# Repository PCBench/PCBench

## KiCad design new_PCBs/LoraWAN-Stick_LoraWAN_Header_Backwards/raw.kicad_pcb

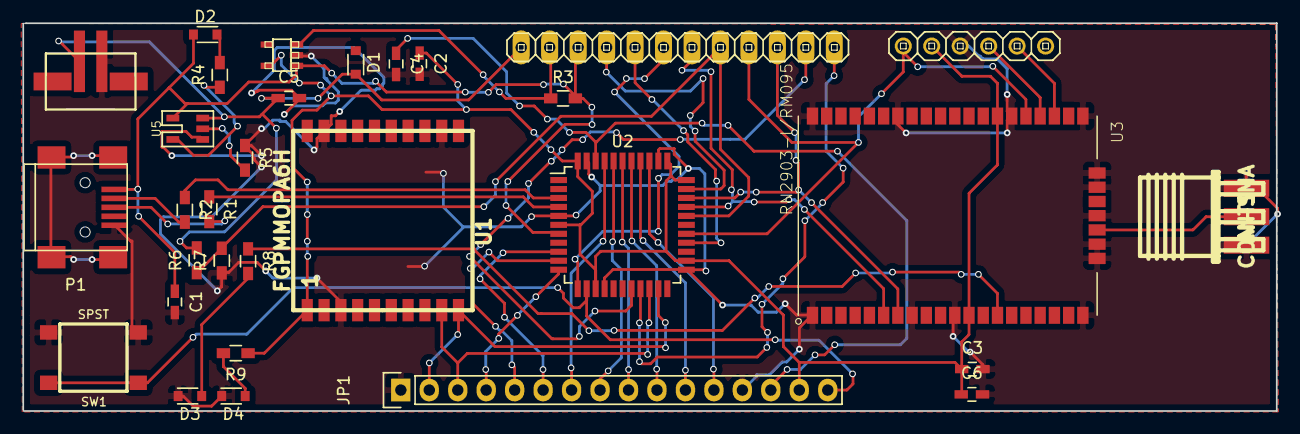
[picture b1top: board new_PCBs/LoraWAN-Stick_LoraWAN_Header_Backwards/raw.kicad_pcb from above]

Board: 2 copper layers, 111.9 x 34.6 mm, 31 parts (0 on the bottom side), 40 nets.

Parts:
ANT1: CON-SMA; CON-SMA-EDGE
C1, C2, C5, C6: 10uF; C_0603_HandSoldering
C3, C4: 1uF; C_0603_HandSoldering
CN1: JST_2PIN-SMT; adafruit-JST-PH-2-SMT
D1: DIODESCH; D_0805
D2: LED-BAT; D_0805
D3: LED-RED; D_0805
D4: LED-POW; D_0805
JP1: CONN_01X16; Pin_Header_Straight_1x16
JP2: PINHD-1X6; adafruit-1X06
JP3: PINHD-1X12; adafruit-1X12
P1: USB_OTG; USB_Mini-B
R1, R2: 22; R_0603_HandSoldering
R3, R6, R7: 100k; R_0603_HandSoldering
R4, R8, R9: 1k; R_0603_HandSoldering
R5: 10k; R_0603_HandSoldering
SW1: SPST; SW_PUSH_SMD
U1: FGPMMOPA6H
U2: ATmega32U4-AU; TQFP-44_10x10mm_Pitch0.8mm
U3: RN2903-I/RM095; XCVR_RN2903-I%2fRM095
U4: SPX3819
U5: MCP73831

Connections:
3v3: C2.1, C3.1, C6.1, JP1.15, JP2.2, R9.1, U1.1, U2.6, U2.14, U2.24, U2.33, U2.34, U2.44, U3.12, U3.34, U4.4
9: JP3.8, R6.1, R7.2, U2.29
/0: JP1.3, U1.9, U2.20
/1: JP1.2, U1.10, U2.21
/2: JP3.12, U2.19
/3: JP3.11, U2.18
/5: JP3.10, U2.31, U3.7
/6: JP2.1, JP3.9, U2.27, U3.32
/10: JP3.7, U2.30, U3.6
/11: JP3.6, U2.12
/12: JP3.5, U2.26
/13: JP3.4, U2.32
/A0: JP1.12, U2.36
/A1: JP1.11, U2.37
/A2: JP1.10, U2.38
/A3: JP1.9, U2.39
/A4: JP1.8, U2.40
/A5: JP1.7, U2.41
/EN: JP3.2, R3.1, U4.3
/MISO: JP1.4, U2.11
/MOSI: JP1.5, U2.10
/SCK: JP1.6, U2.9
/TEST0: JP2.5, U3.30
/TEST1: JP2.4, U3.31
ARFF: C4.1, JP1.14, U2.42
GND: ANT1.2, ANT1.3, ANT1.4, ANT1.5, C1.2, C2.2, C3.2, C4.2, C5.2, C6.2, CN1.1, D3.1, D4.1, JP1.1, JP1.13, JP2.3, P1.5, R5.1, R7.1, SW1.2, U1.3, U1.12, U1.19, U2.5, U2.15, U2.23, U2.35, U2.43, U3.1, U3.8, U3.11, U3.20, U3.21, U3.22, U3.24, U3.26, U3.27, U3.28, U3.33, U3.41, U3.47, U4.2, U5.2
unnamed: ANT1.1, U3.23
unnamed: D2.1, R4.2
unnamed: D3.2, R8.2
unnamed: D4.2, R9.2
unnamed: P1.2, R2.2
unnamed: P1.3, R1.2
unnamed: R1.1, U2.4
unnamed: R2.1, U2.3
unnamed: R4.1, U5.1
unnamed: R5.2, U5.5
unnamed: R8.1, U3.14
RST: JP1.16, SW1.1, U2.13
VBAT: C5.1, CN1.2, D1.1, JP3.1, R6.2, U5.3
VBUS: C1.1, D2.2, JP3.3, P1.1, R3.2, U2.7, U4.1, U5.4

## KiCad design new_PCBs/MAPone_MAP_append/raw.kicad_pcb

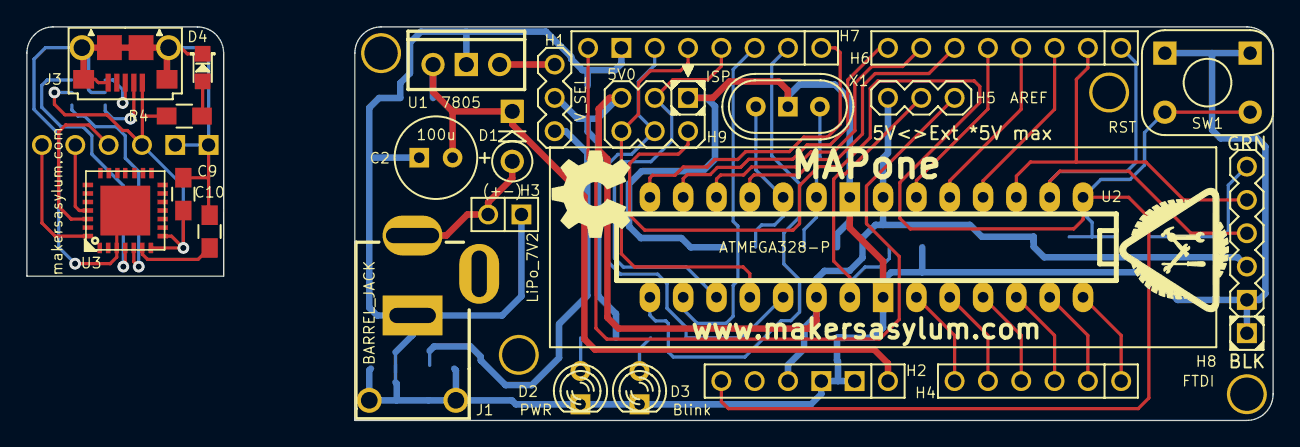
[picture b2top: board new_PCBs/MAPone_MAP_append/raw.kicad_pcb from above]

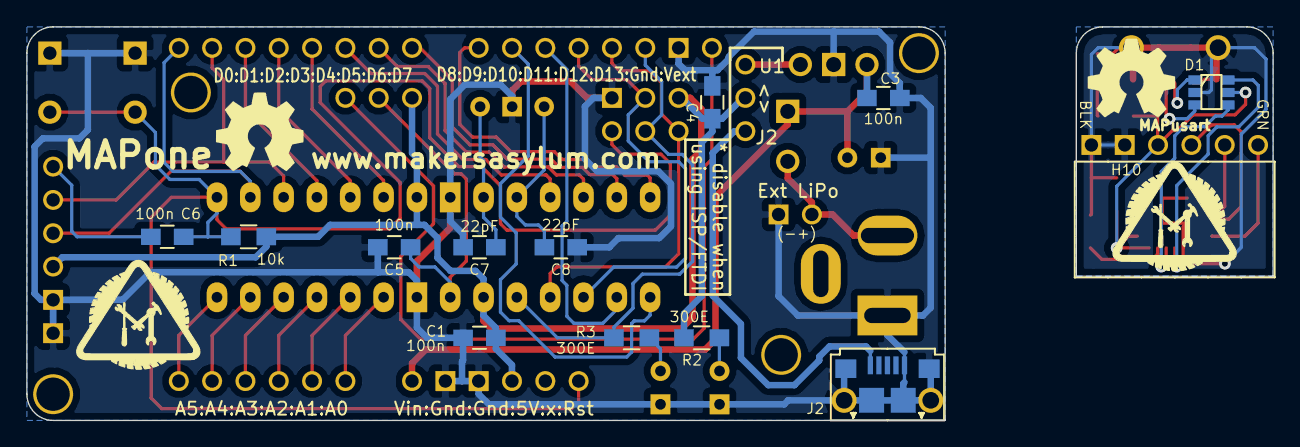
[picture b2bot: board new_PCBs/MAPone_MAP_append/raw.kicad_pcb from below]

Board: 2 copper layers, 70.0 x 30.0 mm, 47 parts (17 on the bottom side), 41 nets.

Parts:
C1, C3, C4, C5, C6, C9, C10: 100n; C_0805_HandSoldering
C2: 100u; Elko_vert_11.2x6.3mm_RM2.5
C7, C8: 22pF; C_0805_HandSoldering
D1: 1N4007; Diode_DO-41_SOD81_Vertical_KathodeUp
D1#2: USBLC6-2; SOT-23-6
D2: PWR; LED-3MM
D3: Blink; LED-3MM
D4: LED_USB; LED-0805
H1: V_SEL; Header_3
H2: Power; Socket_Strip_Straight_1x06
H3: LiPo_7V2; Pin_Header_Straight_1x02
H4: ANALOG; Socket_Strip_Straight_1x06
H5: AREF; Header_A_REF
H6: IO_L; Socket_Strip_Straight_1x08
H7: IO_H; Socket_Strip_Straight_1x08
H8: FTDI; Header_FTDI
H9: ISP; Header_ICSP
H10: FTDI; Socket_Strip_Angled_1x06
J1: BARREL_JACK; JACK_ALIM
J2, J3: USB-Micro; USB_B_Micro
P1, P2, P3, P4: CONN_1; vite_3mm
R1: 10k; R_0805_HandSoldering
R2, R3, R4: 300E; R_0805_HandSoldering
SW1: RST; SW-PB
U1: 7805; LM78XXV
U2: ATMEGA328-P; DIP-28__300_ELL_ZIF
U3: CP210X; qfn-28
X1: 16MHz; Crystal_HC49-U_Vertical_3Pin
Z1, Z2: CONN_1; MA_Logo2
Z3: SCREW; MA_Logo2
Z5: SCREW; OSHW_6mm
Z6, Z7: CONN_1; OSHW_6mm

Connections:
/3V3: C10.1, U3.6
/5V: C1.1, C4.1, C9.1, D1#2.5, H1.2, H2.4, H5.1, H8.3, H9.2, H10.3, J3.1, R1.1, R2.2, R4.1, U2.7, U2.20, U3.7, U3.8
/AD0: H4.6, U2.23
/AD1: H4.5, U2.24
/AD2: H4.4, U2.25
/AD3: H4.3, U2.26
/AD4_SDA: H4.2, U2.27
/AD5_SCL: H4.1, U2.28
/AREF: C5.1, H5.2, U2.21
/D+: D1#2.6, U3.4
/D+IN: D1#2.1, J3.3
/D-: D1#2.4, U3.5
/D-IN: D1#2.3, J3.2
/GND_U: C9.2, C10.2, D1#2.2, D4.2, H10.1, H10.2, J3.5, J3.T1, J3.T2, J3.T3, J3.T4, J3.T5, J3.T6, U3.3, U3.29
/MISO: H7.5, H9.1, U2.18
/MOSI_P: H7.4, H9.4, U2.17
/PB0: H7.1, U2.14
/PB1_P: H7.2, U2.15
/PD2: H6.3, U2.4
/PD3_P: H6.4, U2.5
/PD4: H6.5, U2.6
/PD5_P: H6.6, U2.11
/PD6_P: H6.7, U2.12
/PD7: H6.8, U2.13
/RST: C6.1, H2.6, H9.5, H10.6, R1.2, SW1.2, U2.1, U3.28
/RXD: H6.1, H8.4, H10.5, U2.2, U3.25
/SCK: H7.6, H9.3, R3.1, U2.19
/SS_P: H7.3, U2.16
/TXD: H6.2, H8.5, H10.4, U2.3, U3.26
/V_IN: C2.1, C3.2, D1.2, H2.1, U1.VI
/V_REG: H1.1, U1.VO
/V_USB: H1.3, J2.1
/Vext: H5.3, H7.8
GND: C1.2, C2.2, C3.1, C4.2, C5.2, C7.2, C8.2, D2.2, D3.2, H2.2, H2.3, H3.1, H7.7, H8.1, H8.2, H9.6, J1.2, J2.5, J2.T1, J2.T2, J2.T3, J2.T4, J2.T5, J2.T6, SW1.1, U1.GND, U2.8, U2.22, X1.3
unnamed: C6.2, H8.6
unnamed: C7.1, U2.9, X1.1
unnamed: C8.1, U2.10, X1.2
unnamed: D1.1, H3.2, J1.1
unnamed: D2.1, R2.1
unnamed: D3.1, R3.2
unnamed: D4.1, R4.2

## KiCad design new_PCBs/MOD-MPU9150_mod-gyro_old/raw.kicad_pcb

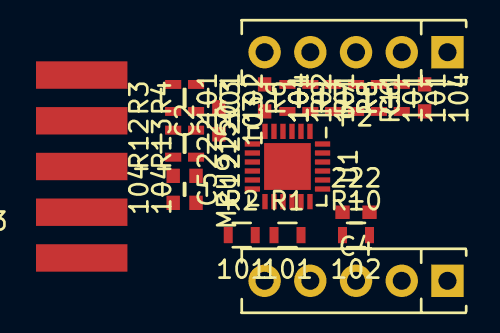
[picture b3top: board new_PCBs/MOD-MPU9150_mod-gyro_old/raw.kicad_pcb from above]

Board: 2 copper layers, 23 parts (0 on the bottom side), 20 nets, no tracks yet.

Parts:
C1, C3, C5, C6: 104; C_0603
C2: 103; C_0603
C4: 222; C_0603
P1, P2: CONN_01X05; SIP5_Housing
P3: HE10-10; UEXTF
R1, R2, R3, R4, R5, R6, R7, R8: 101; R_0603
R9, R10, R11: 102; R_0603
R12, R13: 222; R_0603
U1: MPU9150; QFN-24-1EP_4x4mm_Pitch0.5mm

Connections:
/SCL: P3.5, R4.1, R13.2
/SDA: P3.6, R3.1, R12.2
CLKIN: P2.4, R8.1, R11.1
GND: C1.2, C2.2, C3.2, C4.1, C5.2, C6.2, P1.1, P2.5, P3.2, R9.2, R10.2, R11.2, U1.15, U1.17, U1.18
unnamed: C1.1, U1.10
unnamed: C4.2, U1.20
unnamed: P1.2, R6.2, R9.1
unnamed: P1.3, R2.2
unnamed: P1.4, R1.2
unnamed: P2.2, R5.2
unnamed: P2.3, R7.2, R10.1
unnamed: R1.1, U1.6
unnamed: R2.1, U1.7
unnamed: R3.2, U1.24
unnamed: R4.2, U1.23
unnamed: R5.1, U1.12
unnamed: R6.1, U1.9
unnamed: R7.1, U1.11
unnamed: R8.2, U1.1
VDD: C2.1, C3.1, C5.1, C6.1, P1.5, P2.1, P3.1, R12.1, R13.1, U1.3, U1.8, U1.13

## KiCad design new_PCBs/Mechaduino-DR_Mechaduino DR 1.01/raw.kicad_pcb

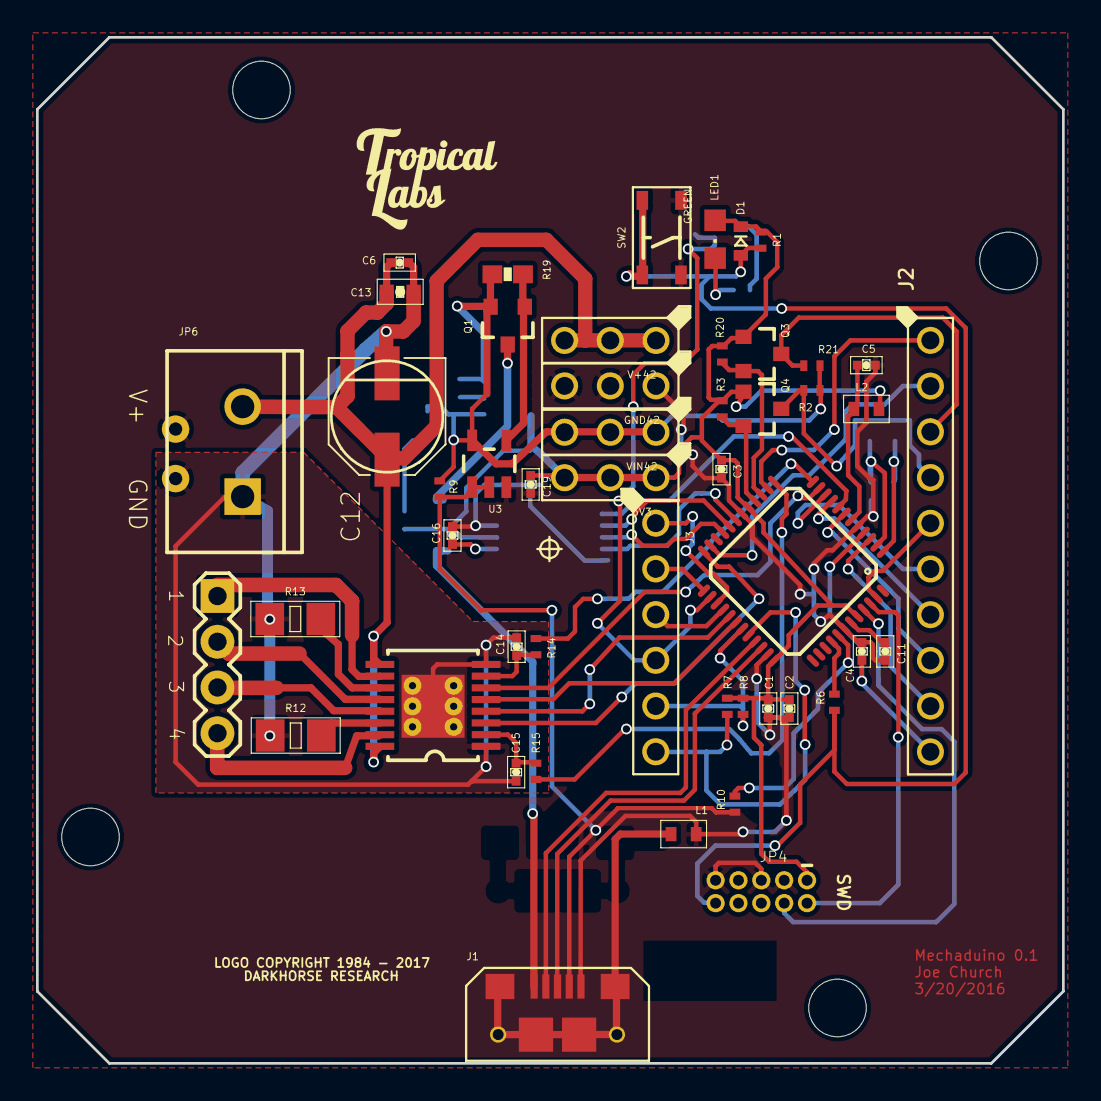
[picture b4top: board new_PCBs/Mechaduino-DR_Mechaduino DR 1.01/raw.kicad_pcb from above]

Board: 2 copper layers, 57.0 x 57.0 mm, 68 parts (0 on the bottom side), 60 nets.

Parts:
3V3: HEADER_01X03_2.54MM
C1, C2, C3, C4, C5, C9, C14, C15, C16, C19: 0.1uF; SWIFT_0402-CAP
C6: 0.01uF; 0402-CAP
C7, C8: 22pF; SWIFT_0402-CAP
C10: 10uF; 0805-CAP
C11, C17: 1uF; SWIFT_0402-CAP
C12: 100uF; CAPACITORS_ELECTROL_6.6X6.6
C13: 1.0uF; 0603-CAP
C18: 10.0uF; C0805
D1: DIODE_SOD-123
F1: 500mA; FUSE_SMD-PTC-1206
FRAME1: FRAME-LEDGER; CREATIVE_COMMONS
GND42: HEADER_01X03_2.54MM
HS: HS; Heat_Sink
IC1: SAMD21G18A-AUT; TQFP48-7X7
J1: USB_MICRO_RIGHT; USB_MICRO-RIGHT
J2: HEADER_01X10_2.54MM; PTH_2.54MM_01X10
J3: HEADER_01X06_2.54MM
JP4: SWD; CONNECTOR_PINHEAD-2X5-P127
JP6: CONNECTORS_M04PTH
L1: INDUCTOR_0603-TDK
L2: BLM18PG471SN1D; 0603-TDK
LED1: GREEN; CHIPLED_0805
MOTOR_POWER42: SCREWTERMINAL-5MM-2
MOT_GRAPHICS_1: WANTAI_57BYGH115-003B; MOT_GRAPHICS_1
Q1: 2.5A 30V; MOSFET_P_CHANNEL_SOT23
Q2: 2N7002PW; DISCRETE_SEMI_SOT323
Q3, Q4: BSS138; MOSFET-N_CHANNEL_SOT23-3
R1, R9, R16: 100K; R0402
R2, R3, R20, R21: 10K; R0402
R5, R6, R10: 330; R0402
R7, R8: 4.7K; R0402
R12, R13: 0.15 ohm; R1206
R14, R15: 1K; R0402
R19: 47K; 0603-RES
SH1: SHORT-HA5; SHORT_ALL-50
SW2: TACT_4.2MM
U1: AS5047D_TSSOP14
U2: ALLEGRO_A4954_TSSOP16
U3: 74AHC1G125; DIGITAL_IC_SOT23-5
U4: 3.3V_REG; SOT23-5_1
U$3: TROPICAL_LABS_LOGO_1LOGO3; LOGO3
U$5: MECHADUINO_LOGO
V+42: HEADER_01X03_2.54MM
VIN42: HEADER_01X03_2.54MM
Y1: 32,768Khz; CRYSTAL-SMD-2.0X1.2

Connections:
3.3V: 3V3.P$1, 3V3.P$2, 3V3.P$3, C1.1, C2.1, C3.1, C10.1, C17.1, C19.1, D1.K, IC1.17, IC1.36, IC1.44, JP4.1, L2.1, LED1.A, Q3.1, Q4.1, R1.1, R3.1, R7.1, R8.1, R20.1, U1.12, U4.5
/ARDUINO_A0: IC1.3, J2.P$9
/ARDUINO_A1: IC1.7, J2.P$8
/ARDUINO_A2----HEADER_SS: IC1.8, U1.1
/ARDUINO_A3: IC1.9, J2.P$7
/ARDUINO_A4: IC1.10, J2.P$6
/ARDUINO_A5: IC1.47, J2.P$5
/ARDUINO_AREF: C4.1, IC1.4, J2.P$10
/ARDUINO_D0: IC1.16, Q4.2, R3.2
/ARDUINO_D1: IC1.15, Q3.2, R20.2
/ARDUINO_D2: IC1.23, J2.P$2
/ARDUINO_D3: IC1.14, J2.P$1
/ARDUINO_D4----VREF2: IC1.13, R15.2
/ARDUINO_D5----IN3: IC1.24, U2.3
/ARDUINO_D6----IN4: IC1.29, U2.4
/ARDUINO_D7----IN2: IC1.30, U2.5
/ARDUINO_D8----IN1: IC1.11, U2.6
/ARDUINO_D9----VREF1: IC1.12, R14.2
/ARDUINO_D10_SS: IC1.27, J3.P$1
/ARDUINO_D11_MOSI: IC1.25, J3.P$2
/ARDUINO_D12_MISO: IC1.28, J3.P$3
/ARDUINO_D13_SCK: IC1.26, J3.P$4, Q2.1, R16.1
/ARDUINO_D20_SDA: IC1.31, J3.P$5, R8.2
/ARDUINO_D21_SCL: IC1.32, J3.P$6, R7.2
/HEADER_MISO: IC1.21, U1.3
/HEADER_MOSI: IC1.19, U1.4
/HEADER_SCK: IC1.20, U1.2
/HV1: J2.P$3, Q3.3, R21.2
/HV2: J2.P$4, Q4.3, R2.2
/N$1: LED1.C, R5.1
/N$2: R12.2, U2.14
/N$3: Q2.3, R5.2
/N$4: R13.2, U2.11
/N$6: C15.1, R15.1, U2.2
/N$7: J1.4, R9.2, R10.1, U3.1, U3.2
/N$13: JP6.4, U2.15
/N$14: JP6.1, U2.10
/N$15: JP6.2, U2.12
/N$16: JP6.3, U2.13
/N$27: C16.1, U1.11
/N$32: C14.1, R14.1, U2.7
/N$33: F1.2, Q1.3
/N$34: Q1.1, R19.2, U3.4
/N$36: F1.1, J1.1
/PA00_XIN32: C7.2, IC1.1, Y1.2
/PA01_XOUT32: C8.2, IC1.2, Y1.1
/PA28_USB_HOST_EN: IC1.41, R10.2
/PA30_SWCLK: IC1.45, JP4.4
/PA31_SWDIO: IC1.46, JP4.2
/RESET: D1.A, JP4.10, R1.2, R6.1, SW2.P$1, SW2.P$2
/TARGET_RESET_EDBG: IC1.40, R6.2
/TARGET_USB_N: IC1.33, J1.2
/TARGET_USB_P: IC1.34, J1.3
/VDDANA: C5.1, IC1.6, L2.2
/VDDCORE: C11.1, IC1.43
GND: C1.2, C2.2, C3.2, C4.2, C5.2, C7.1, C8.1, C9.2, C10.2, C11.2, C16.2, C17.2, C18.2, C19.2, GND42.P$1, GND42.P$2, GND42.P$3, IC1.5, IC1.18, IC1.35, IC1.42, J1.5, JP4.3, JP4.5, JP4.9, L1.2, Q2.2, R16.2, SH1.2, SW2.P$3, SW2.P$4, U1.5, U1.13, U3.3, U4.2
GND2: C6.2, C12.-, C13.2, C14.2, C15.2, HS.HS, HS.~, MOTOR_POWER42.1, R12.1, R13.1, SH1.1, U2.1, U2.8
SLD: J1.S1, J1.S2, J1.S3, J1.S4, J1.S5, J1.S6, L1.1
V+: C6.1, C12.+, C13.1, MOTOR_POWER42.2, U2.9, U2.16, V+42.P$1, V+42.P$2, V+42.P$3
VIN: C9.1, C18.1, Q1.2, R2.1, R9.1, R19.1, R21.1, U3.5, U4.1, U4.3, VIN42.P$1, VIN42.P$2, VIN42.P$3

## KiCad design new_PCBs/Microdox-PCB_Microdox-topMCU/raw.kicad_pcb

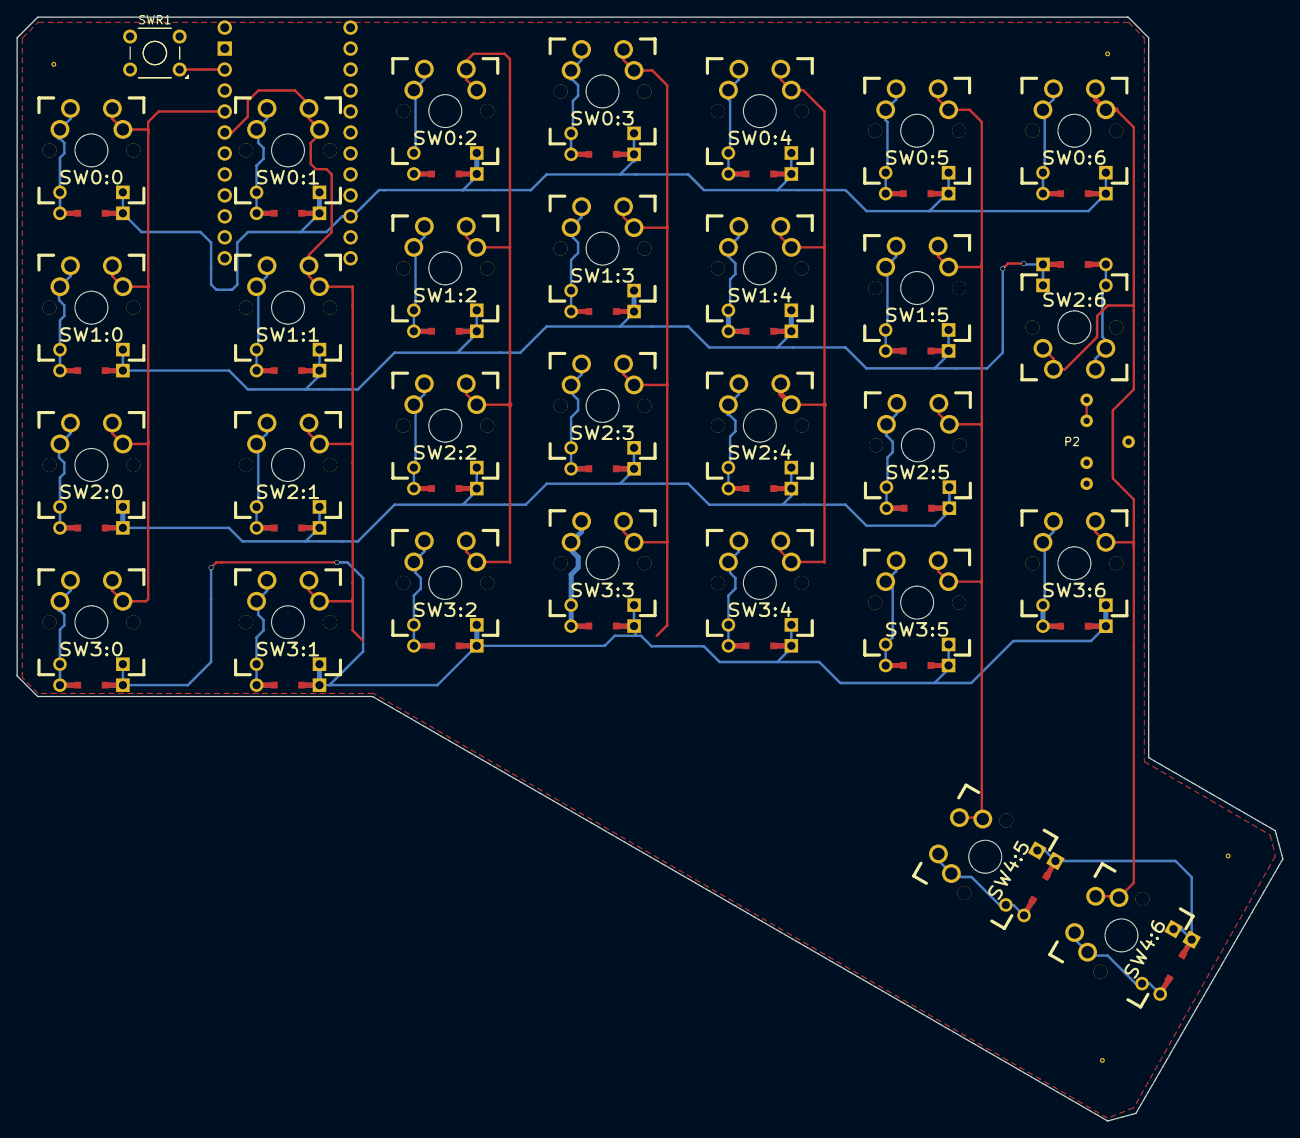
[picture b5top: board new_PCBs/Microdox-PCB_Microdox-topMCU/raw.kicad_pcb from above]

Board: 2 copper layers, 153.3 x 133.7 mm, 32 parts (1 on the bottom side), 45 nets.

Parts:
P2: CONN_01X03; 3mmJack
PM1: PROMICRO
SW0:0, SW0:1, SW0:2, SW0:3, SW0:4, SW0:5, SW0:6, SW1:0, SW1:1, SW1:2, SW1:3, SW1:4, SW1:5, SW2:0, SW2:1, SW2:2, SW2:3, SW2:4, SW2:5, SW2:6, SW3:0, SW3:1, SW3:2, SW3:3, SW3:4, SW3:5, SW3:6, SW4:5, SW4:6: MX_FLIP_DIODE
SWR1: SW_PUSH; SW_TH_Tactile_Omron_B3F-10xx

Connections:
/COL0: PM1.16, SW0:0.1, SW1:0.1, SW2:0.1, SW3:0.1
/COL1: PM1.17, SW0:1.1, SW1:1.1, SW2:1.1, SW3:1.1
/COL2: PM1.18, SW0:2.1, SW1:2.1, SW2:2.1, SW3:2.1
/COL3: PM1.20, SW0:3.1, SW1:3.1, SW2:3.1, SW3:3.1
/COL4: PM1.21, SW0:4.1, SW1:4.1, SW2:4.1, SW3:4.1
/COL5: PM1.11, SW0:5.1, SW1:5.1, SW2:5.1, SW3:5.1, SW4:5.1
/COL6: PM1.23, SW0:6.1, SW2:6.1, SW3:6.1, SW4:6.1
/ROW0: PM1.9, SW0:0.4, SW0:1.4, SW0:2.4, SW0:3.4, SW0:4.4, SW0:5.4, SW0:6.4
/ROW1: PM1.8, SW1:0.4, SW1:1.4, SW1:2.4, SW1:3.4, SW1:4.4, SW1:5.4, SW2:6.4
/ROW2: PM1.7, SW2:0.4, SW2:1.4, SW2:2.4, SW2:3.4, SW2:4.4, SW2:5.4
/ROW3: PM1.6, SW3:0.4, SW3:1.4, SW3:2.4, SW3:3.4, SW3:4.4, SW3:5.4, SW3:6.4
/ROW4: PM1.10, SW4:5.4, SW4:6.4
/RST: PM1.14, SWR1.1
/SER: P2.2, PM1.5
GND: P2.3, PM1.2, PM1.3, PM1.13, SWR1.2
unnamed: SW0:0.2, SW0:0.3
unnamed: SW0:1.2, SW0:1.3
unnamed: SW0:2.2, SW0:2.3
unnamed: SW0:3.2, SW0:3.3
unnamed: SW0:4.2, SW0:4.3
unnamed: SW0:5.2, SW0:5.3
unnamed: SW0:6.2, SW0:6.3
unnamed: SW1:0.2, SW1:0.3
unnamed: SW1:1.2, SW1:1.3
unnamed: SW1:2.2, SW1:2.3
unnamed: SW1:3.2, SW1:3.3
unnamed: SW1:4.2, SW1:4.3
unnamed: SW1:5.2, SW1:5.3
unnamed: SW2:0.2, SW2:0.3
unnamed: SW2:1.2, SW2:1.3
unnamed: SW2:2.2, SW2:2.3
unnamed: SW2:3.2, SW2:3.3
unnamed: SW2:4.2, SW2:4.3
unnamed: SW2:5.2, SW2:5.3
unnamed: SW2:6.2, SW2:6.3
unnamed: SW3:0.2, SW3:0.3
unnamed: SW3:1.2, SW3:1.3
unnamed: SW3:2.2, SW3:2.3
unnamed: SW3:3.2, SW3:3.3
unnamed: SW3:4.2, SW3:4.3
unnamed: SW3:5.2, SW3:5.3
unnamed: SW3:6.2, SW3:6.3
unnamed: SW4:5.2, SW4:5.3
unnamed: SW4:6.2, SW4:6.3
VCC: P2.1, PM1.15

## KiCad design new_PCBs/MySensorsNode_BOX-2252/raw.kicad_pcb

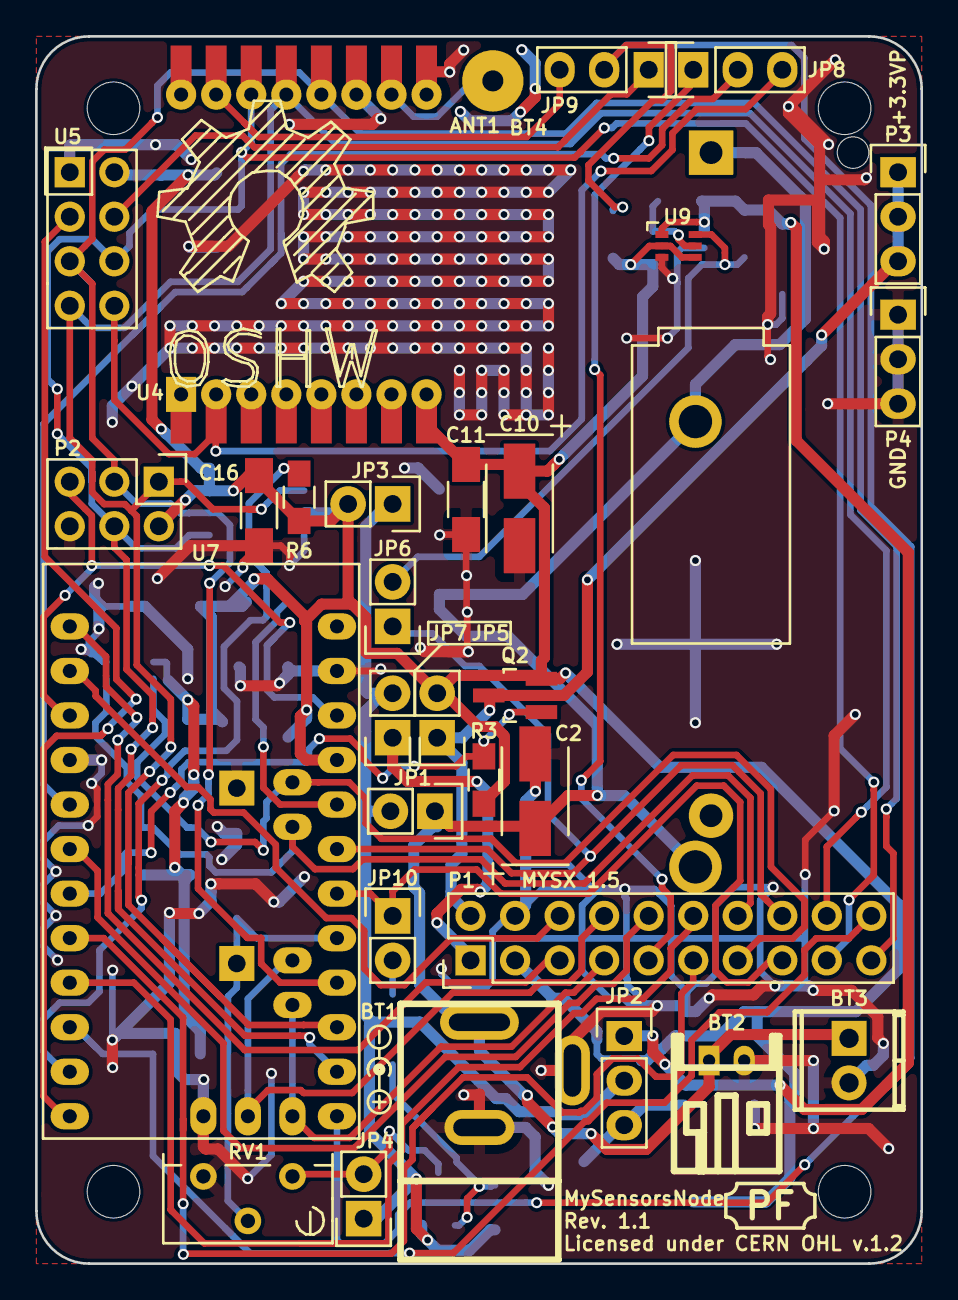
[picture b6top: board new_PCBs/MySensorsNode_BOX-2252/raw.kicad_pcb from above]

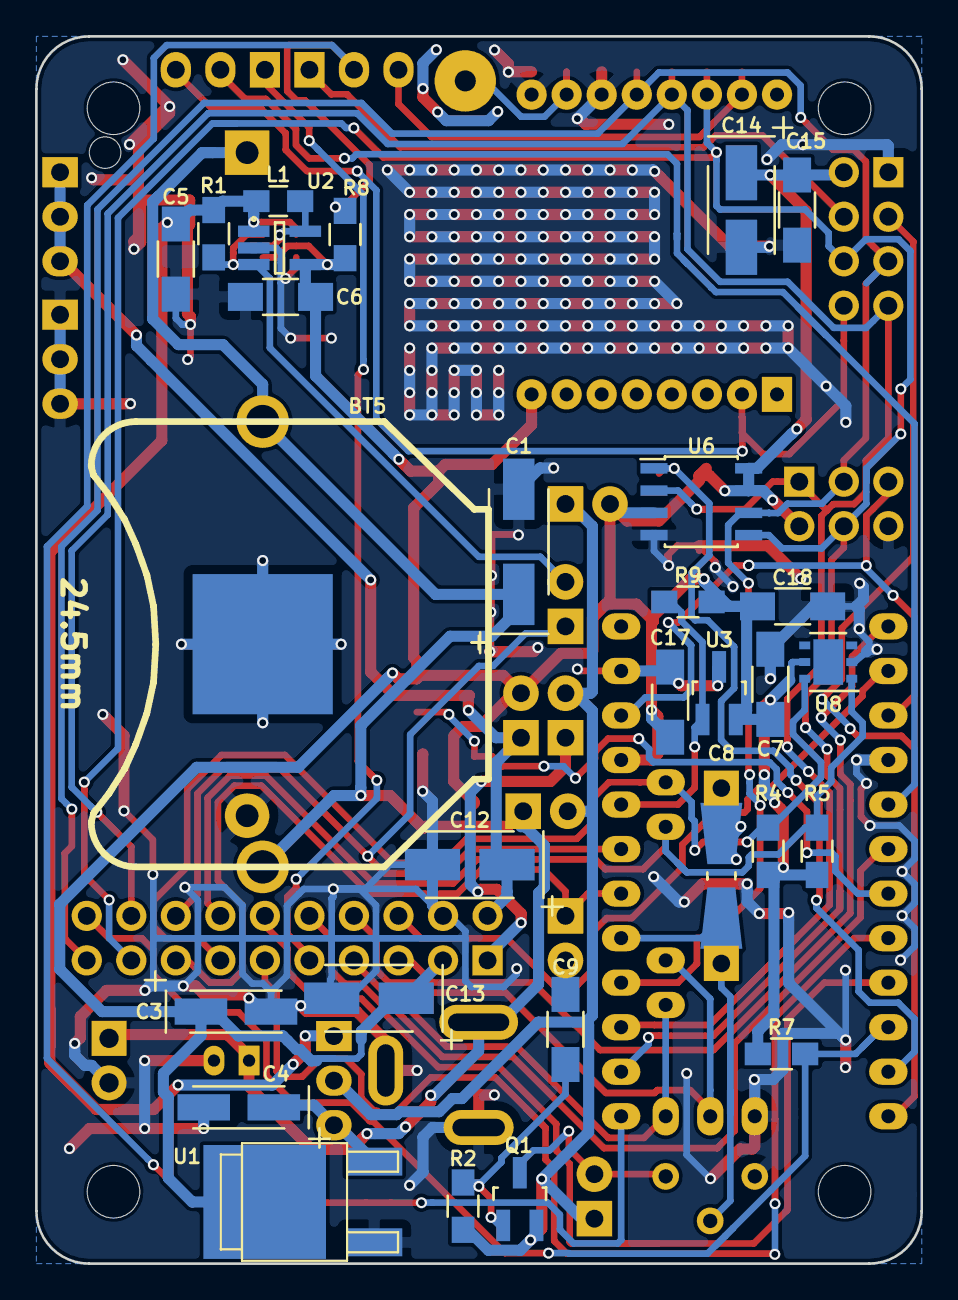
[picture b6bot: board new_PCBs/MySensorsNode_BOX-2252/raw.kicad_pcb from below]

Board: 2 copper layers, 50.5 x 70.0 mm, 66 parts (29 on the bottom side), 41 nets.

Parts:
ANT1: CONN_01X01; SolderWirePad_single_1-2mmDrill
BT1: 2.5mm jack; dc_socket-kcswalter
BT2: JST; s2b-ph-kl-kcswalter
BT3: Generic; TerminalBlock2.54mmx2-kcswalter
BT4: CR123; CR123_holder
BT5: 24.5mm; keystone_3009-kcswalter
C1: 47uF; TantalC_SizeC_EIA-6032_HandSoldering
C2, C10, C12, C13, C14: 4.7uF; TantalC_SizeB_EIA-3528_HandSoldering
C3, C4: 10uF; TantalC_SizeA_EIA-3216_HandSoldering
C5, C6: 10uF; C_1206_HandSoldering
C7, C9, C11, C15, C16, C17, C18: 0.1uF; C_1206_HandSoldering
C8: C; Resistor_SMD+THTuniversal_0805to1206_RM10_HandSoldering
HOLE1, HOLE2, HOLE3, HOLE4: MountingHole_3mm
JP1, JP3, JP4, JP5, JP6, JP7, JP10: Jumper_NO_Small; Pin_Header_Straight_1x02
JP2, JP8, JP9: JUMPER3; Pin_Header_Straight_1x03
L1: 4.7uH; C_0805_HandSoldering
OSHW_LOGO: Symbol_OSHW-Logo_SilkScreen_BIG
P1: MYSX_1.5
P2: CONN_02X03; Pin_Header_Straight_2x03
P3, P4: CONN_01X03; Pin_Header_Straight_1x03
PLUG_SPEC: LOGO; Logo_silk_polarity_center_5x1.4mm
Q1, Q2: DMP3056L-7; SOT-23_Handsoldering
R1: 150K; R_0805_HandSoldering
R2, R3, R4, R5: 10K; R_0805_HandSoldering
R6, R7, R8, R9: 56K; R_0805_HandSoldering
RV1: 1M; Potentiometer_Bourns_3296Y_3-8Zoll_Angular_ScrewUp
U1: LD1117DT33TR; d-pak-kcswalter
U2: TPS61097A; SOT-23-5_Handsoldering
U3: ATSHA204A; SOT-23_Handsoldering
U4: RFM69HW; RFM69HW_SMD_ThroughHole_Handsoldering
U5: NRF24L01
U6: AT25DF512C; SOIC-8_3.9x4.9mm_Pitch1.27mm
U7: ArduinoProMini; pro_mini
U8: Si7021; DFN-6-1EP_3x3mm_Pitch0.95mm
U9: TPS61221; SC-70-6

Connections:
+3.3VP: C12.1, JP5.1, P1.2, P3.1, P3.2, P3.3, Q2.3
+3V3: C3.1, C6.1, C7.1, C10.1, C11.2, C13.1, C14.1, C15.2, C16.2, C17.1, C18.1, JP3.2, JP5.2, P1.3, P2.2, Q2.2, R3.2, R4.2, R5.2, R6.2, R7.2, R8.1, R9.2, U1.2, U2.4, U3.2, U4.8, U5.2, U6.3, U6.7, U6.8, U7.21, U8.5, U9.2, U9.4
+BATT: JP1.2, JP2.2, JP3.1, JP4.1, JP7.2, Q1.2, R2.2
/MISO: P1.18, P2.1, U4.13, U5.7, U6.2, U7.15
/MOSI: P1.17, P2.4, U4.14, U5.6, U6.5, U7.14
/SCK: P1.19, P2.3, U4.12, U5.5, U6.6, U7.16
ATSHA_SDA: R9.1, U3.1, U7.20
FLASH_CSN: R6.1, U6.1, U7.11
GND: BT1.1, BT1.2, BT2.2, BT3.2, BT4.2, BT5.2, C1.2, C2.2, C3.2, C4.2, C5.2, C6.2, C7.2, C8.2, C10.2, C11.1, C12.2, C13.2, C14.2, C15.1, C16.1, C17.2, C18.2, P1.4, P2.6, P4.1, P4.2, P4.3, RV1.3, U1.1, U2.2, U3.3, U4.9, U4.11, U5.1, U6.4, U7.4, U7.23, U7.29, U8.2, U9.3
MYSX_3.3V_EN: Q2.1, R3.1, U7.7
MYSX_A1: P1.7, U7.27
MYSX_A2: P1.8, U7.28
MYSX_D1_DFM: P1.5, U7.1
MYSX_D2_DTM: P1.6, U7.2
MYSX_D3_INT: JP8.1, P1.9
MYSX_D4_INT: P1.10, U7.6
MYSX_D5_PWM: P1.11, U7.8
MYSX_D6_PWM: P1.12, U7.9
MYSX_D7_SCL: P1.13, R4.1, U7.26, U8.6
MYSX_D8_SDA: P1.14, R5.1, U7.25, U8.1
MYSX_D9_A3: JP10.1, P1.15, U7.18
MYSX_D10_A4: JP6.1, P1.16, U7.19
MYSX_D14_CS: P1.20, R7.1, U7.10
unnamed: ANT1.1, U4.10
unnamed: BT1.3, BT2.1, BT3.1, BT4.1, BT5.1, C1.1, C2.1, JP1.1
unnamed: C4.1, JP2.3, U1.3
unnamed: C5.1, JP2.1, L1.2, R1.1, U2.1, U9.1
unnamed: C9.1, JP10.2
unnamed: C9.2, Q1.1, R2.1
unnamed: JP4.2, Q1.3, RV1.1
unnamed: JP6.2, R1.2, U2.3, U9.6
unnamed: JP7.1, P1.1
unnamed: JP8.2, U7.5
unnamed: JP9.2, R8.2, U7.13
unnamed: L1.1, U2.5, U9.5
RESET: P2.5, U7.3, U7.22
RF24_CE: U5.3, U7.12
RF24_CSN: JP9.1, U5.4
RF69_NSS: JP9.3, U4.15
RF_INT: JP8.3, U4.2, U5.8
VBAT_SMPL: C8.1, RV1.2, U7.17

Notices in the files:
new_PCBs/MySensorsNode_BOX-2252/raw.kicad_pcb:
Copyright (c) 2015 Patrick Fallberg
Licensed under CERN OHL v.1.2
parts and their libraries:
Released under the Creative Commons Attribution Share-Alike 4.0 License
https://creativecommons.org/licenses/by-sa/4.0
